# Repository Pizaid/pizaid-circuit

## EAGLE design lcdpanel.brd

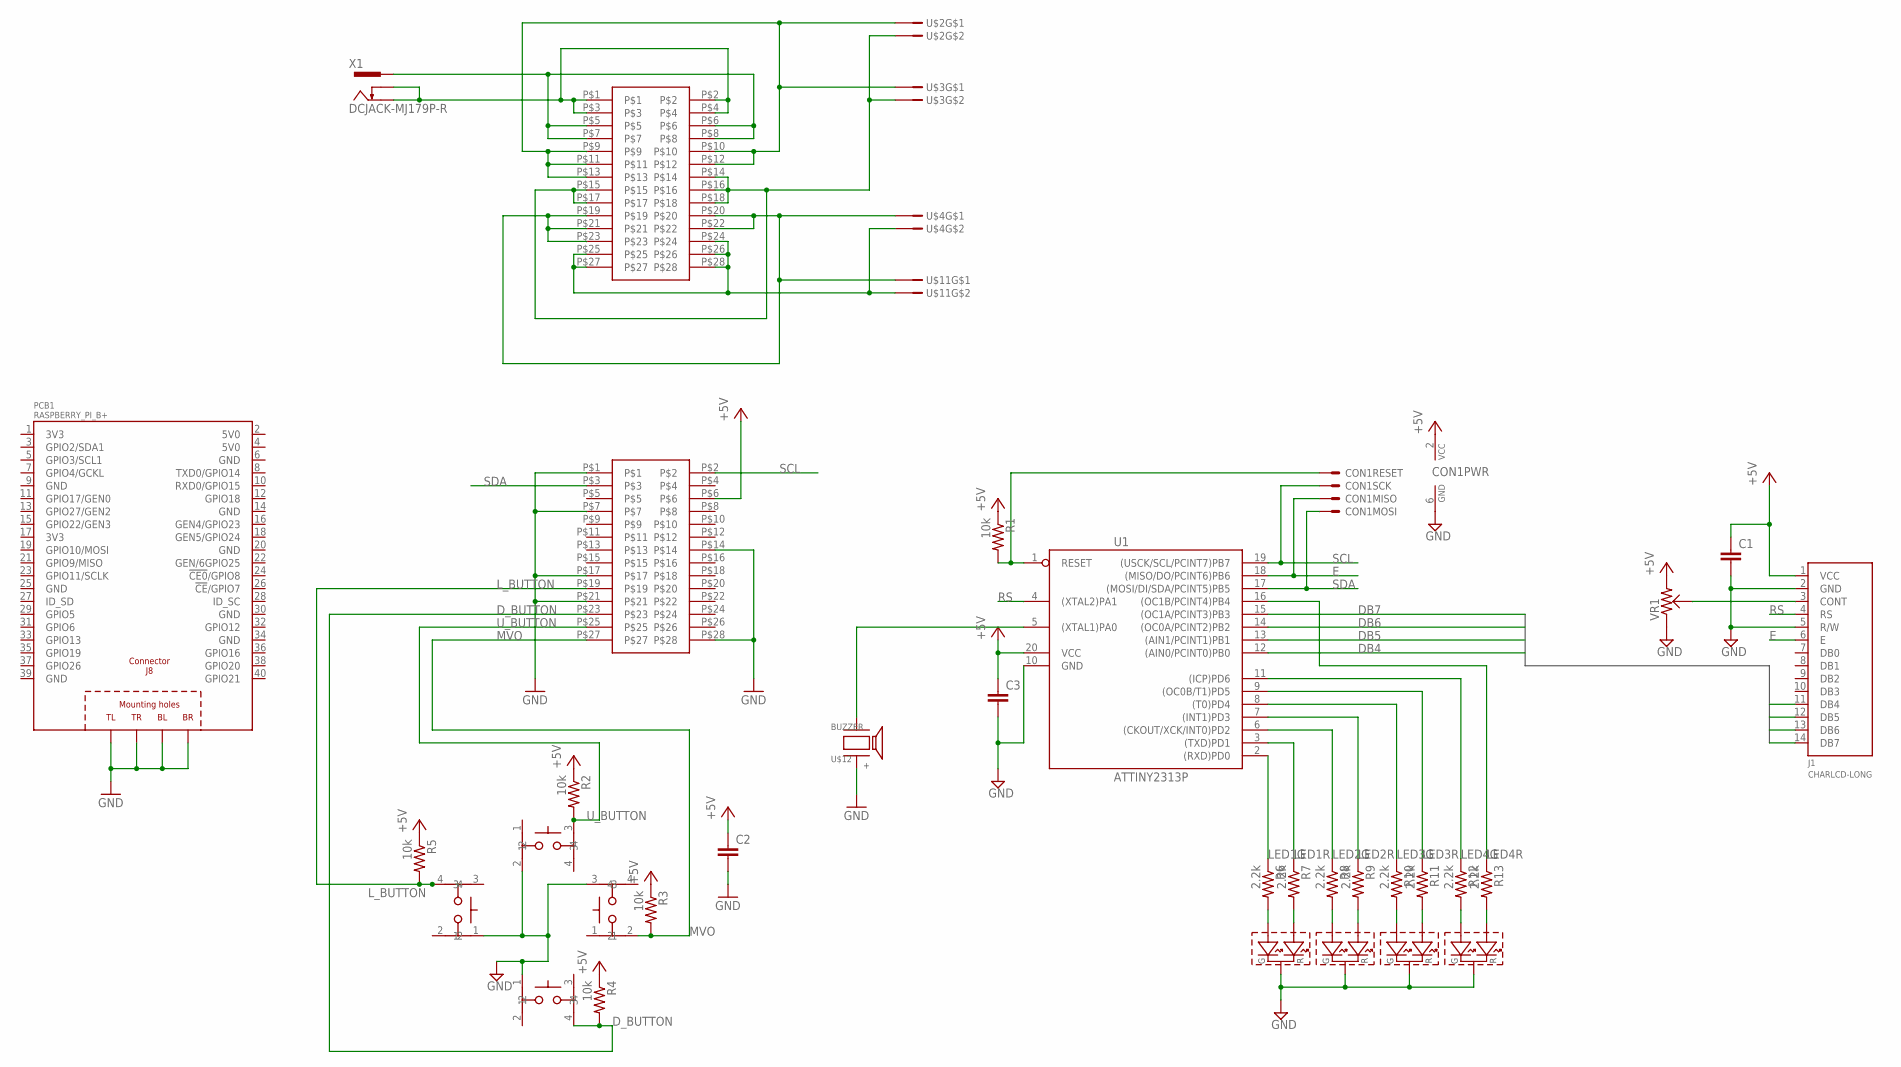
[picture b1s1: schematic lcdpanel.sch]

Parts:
C1, C2, C3: C-EUC0603; C0603
CON1: AVRISP-NEWSYMBOL-ML6; ML6
D1, D2, D3, D4: LED-RG-3MM; LED-2COL-3MM
J1: CHARLCD-LONG; CHARLCD-7X2-LONG
PCB1: RASPBERRY_PI_B+
R1, R2, R3, R4, R5: 10k; 1608
R6, R7, R8, R9, R10, R11, R12, R13: 2.2k; 1608
SW1, SW2, SW3, SW4: PUSHSW
U1: ATTINY2313P; DIL20
U$2, U$3, U$4, U$11: B2P-VH
U$12: BUZZER
U$13, U$14: CON_14X2
VR1: VR; VR-637A
X1: DCJACK-MJ179P-R; MJ-179P-R

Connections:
+5V: C1.1, C2.1, C3.1, CON1.2 (VCC), J1.1 (VCC), R1.1, R2.1, R3.1, R4.1, R5.1, U1.20 (VCC), U$13.P$6, VR1.2
DB4: J1.11 (DB4), U1.12 ((AIN0/PCINT0)PB0)
DB5: J1.12 (DB5), U1.13 ((AIN1/PCINT1)PB1)
DB6: J1.13 (DB6), U1.14 ((OC0A/PCINT2)PB2)
DB7: J1.14 (DB7), U1.15 ((OC1A/PCINT3)PB3)
D_BUTTON: R4.2, SW4.4, U$13.P$23
E: CON1.1 (S), J1.6 (E), U1.18 ((MISO/DO/PCINT6)PB6)
GND: C1.2, C2.2, C3.2, CON1.6 (GND), D1.K, D2.K, D3.K, D4.K, J1.2 (GND), J1.5 (R/W), PCB1.PE_BL (BL), PCB1.PE_BR (BR), PCB1.PE_TL (TL), PCB1.PE_TR (TR), SW1.2, SW2.1, SW3.3, SW4.1, U1.10 (GND), U$12.+, U$13.P$1, U$13.P$7, U$13.P$14, U$13.P$17, U$13.P$21, U$13.P$28, VR1.1
LED1G: R6.1, U1.2 ((RXD)PD0)
LED1R: R7.1, U1.3 ((TXD)PD1)
LED2G: R8.1, U1.6 ((CKOUT/XCK/INT0)PD2)
LED2R: R9.1, U1.7 ((INT1)PD3)
LED3G: R10.1, U1.8 ((T0)PD4)
LED3R: R11.1, U1.9 ((OC0B/T1)PD5)
LED4G: R12.1, U1.11 ((ICP)PD6)
LED4R: R13.1, U1.16 ((OC1B/PCINT4)PB4)
L_BUTTON: R5.2, SW2.4, U$13.P$19
MVO: R3.2, SW3.2, U$13.P$27
unnamed: CON1.5 (S), R1.2, U1.1 (RESET)
unnamed: U1.5 ((XTAL1)PA0), U$12.-
unnamed: J1.3 (CONT), VR1.BR
unnamed: D1.YG (G_A), R6.2
unnamed: D1.R (R_A), R7.2
unnamed: D2.YG (G_A), R8.2
unnamed: D3.YG (G_A), R10.2
unnamed: D3.R (R_A), R11.2
unnamed: D4.YG (G_A), R12.2
unnamed: D4.R (R_A), R13.2
unnamed: D2.R (R_A), R9.2
unnamed: U$14.P$5, U$14.P$6, U$14.P$7, U$14.P$8, X1.1
unnamed: U$2.P$1, U$3.P$1, U$14.P$9, U$14.P$10, U$14.P$11, U$14.P$12, U$14.P$13
unnamed: U$2.P$2, U$3.P$2, U$14.P$14, U$14.P$15, U$14.P$16, U$14.P$17, U$14.P$18
unnamed: U$4.P$2, U$11.P$2, U$14.P$24, U$14.P$25, U$14.P$26, U$14.P$27, U$14.P$28
unnamed: U$14.P$1, U$14.P$2, U$14.P$3, U$14.P$4, X1.2, X1.3
unnamed: U$4.P$1, U$11.P$1, U$14.P$19, U$14.P$20, U$14.P$21, U$14.P$22, U$14.P$23
RS: J1.4 (RS), U1.4 ((XTAL2)PA1)
SCL: CON1.3 (S), U1.19 ((USCK/SCL/PCINT7)PB7), U$13.P$2
SDA: CON1.4 (S), U1.17 ((MOSI/DI/SDA/PCINT5)PB5), U$13.P$3
U_BUTTON: R2.2, SW1.3, U$13.P$25

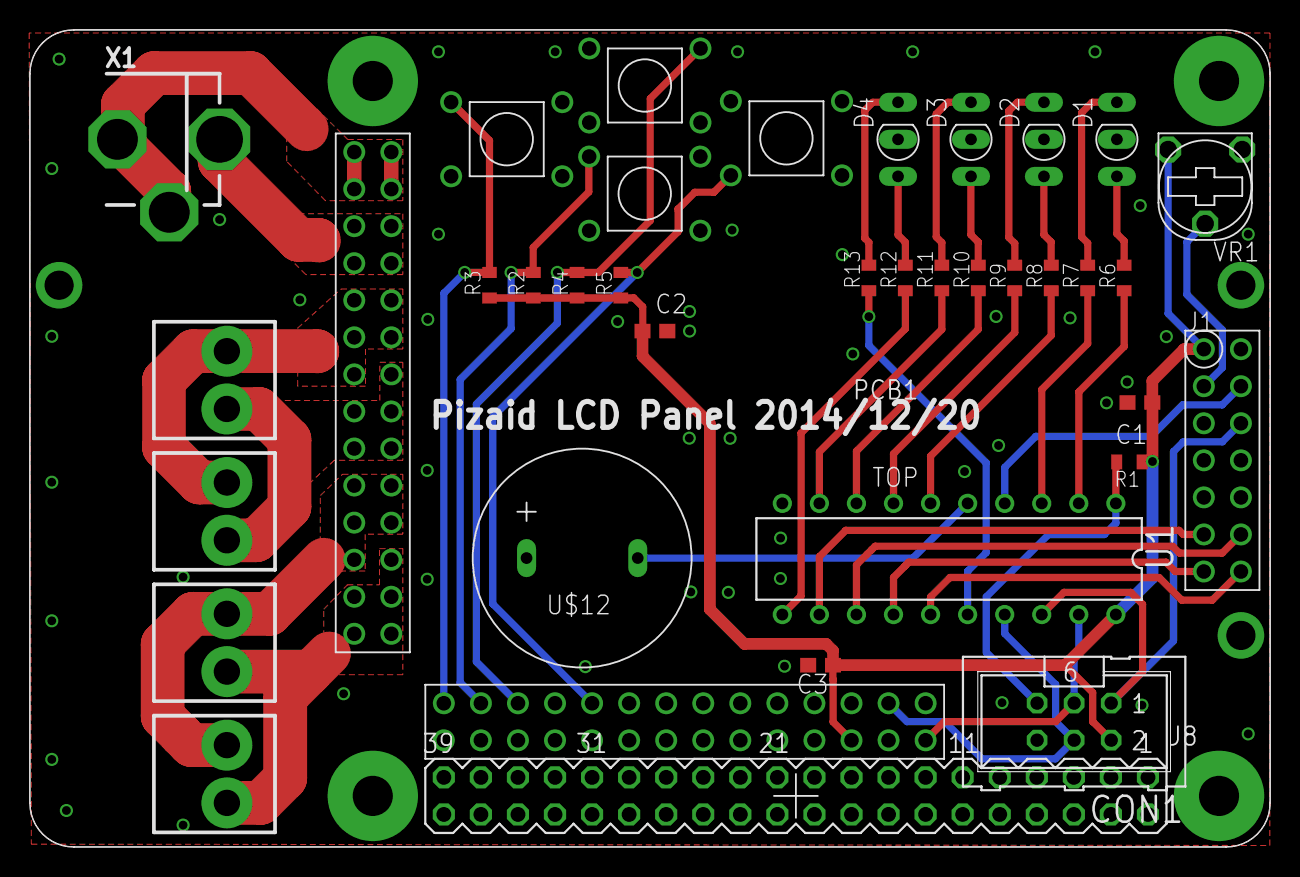
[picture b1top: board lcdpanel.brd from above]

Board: 2 copper layers, 85.0 x 56.0 mm, 37 parts (0 on the bottom side), 39 nets.

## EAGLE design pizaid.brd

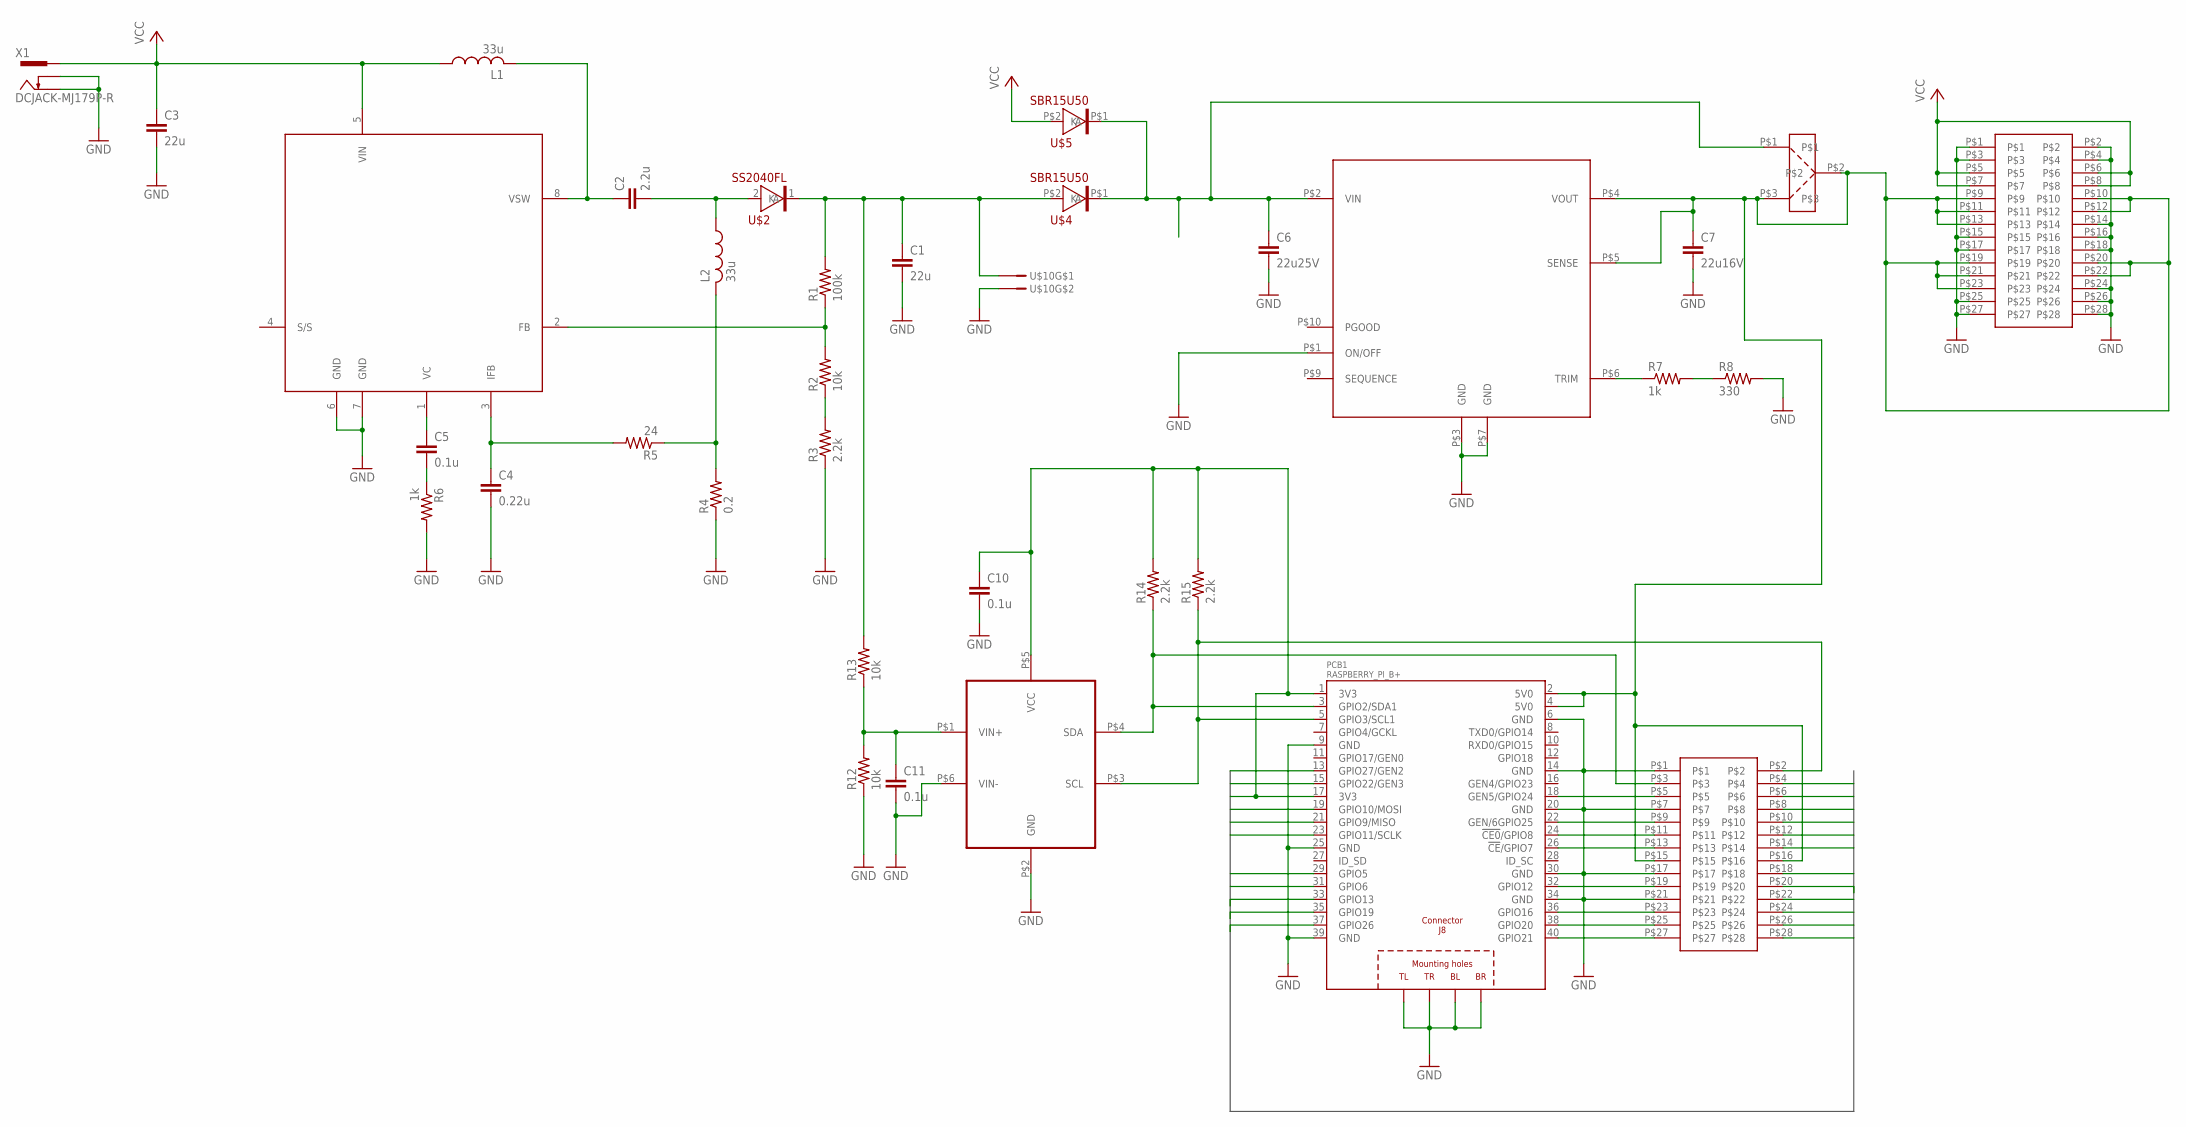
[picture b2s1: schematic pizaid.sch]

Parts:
C1, C3: 22u; C3225
C2: 2.2u; C3216
C4: 0.22u; C0603
C5, C10, C11: 0.1u; C0603
C6: 22u25V; C3225
C7: 22u16V; C3225
L1, L2: 33u; L5650M
PCB1: RASPBERRY_PI_B+
R1: 100k; R0603
R2, R12, R13: 10k; R0603
R3, R14, R15: 2.2k; R0603
R4: 0.2; 0207/15
R5: 24; R0603
R6, R7: 1k; R0603
R8: 330; R0603
U$1: LT1512CS8; SOP8
U$2: SS2040FL; SOD-123FL
U$3, U$8: CON_14X2
U$4, U$5: SBR15U50; POWERDI5
U$6: OKL-T/6
U$9: MCP3425; SOT-23-6
U$10: B2P-VH
U$11: SELECT_PAD
X1: DCJACK-MJ179P-R; MJ-179P-R

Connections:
5V0@2: C7.1, PCB1.2 (5V0), PCB1.4 (5V0), U$3.P$9, U$3.P$10, U$3.P$11, U$3.P$12, U$3.P$13, U$3.P$19, U$3.P$20, U$3.P$21, U$3.P$22, U$3.P$23, U$6.P$4 (VOUT), U$6.P$5 (SENSE), U$8.P$15, U$8.P$16, U$11.P$2, U$11.P$3
B1: PCB1.15 (GPIO22/GEN3), U$8.P$4
B2: C10.1, PCB1.1 (3V3), PCB1.17 (3V3), R14.2, R15.2, U$8.P$6, U$9.P$5 (VCC)
B3: PCB1.19 (GPIO10/MOSI), U$8.P$8
B4: PCB1.21 (GPIO9/MISO), U$8.P$10
B5: PCB1.23 (GPIO11/SCLK), U$8.P$12
B6: U$8.P$14
B8: PCB1.29 (GPIO5), U$8.P$18
B9: PCB1.31 (GPIO6), U$8.P$20
B10: PCB1.33 (GPIO13), U$8.P$22
B11: PCB1.35 (GPIO19), U$8.P$24
B12: PCB1.37 (GPIO26), U$8.P$26
B13: U$8.P$28
B$1: PCB1.13 (GPIO27/GEN2)
GIRD: C6.1, U$4.P$1 (K), U$5.P$1 (K), U$6.P$2 (VIN), U$11.P$1
GND: C1.2, C3.2, C4.2, C6.2, C7.2, C10.2, C11.2, PCB1.6 (GND), PCB1.9 (GND), PCB1.14 (GND), PCB1.20 (GND), PCB1.25 (GND), PCB1.30 (GND), PCB1.34 (GND), PCB1.39 (GND), PCB1.PE_BL (BL), PCB1.PE_BR (BR), PCB1.PE_TL (TL), PCB1.PE_TR (TR), R3.1, R4.1, R6.2, R8.2, R12.1, U$1.6 (GND), U$1.7 (GND), U$3.P$1, U$3.P$2, U$3.P$3, U$3.P$4, U$3.P$14, U$3.P$15, U$3.P$16, U$3.P$17, U$3.P$18, U$3.P$24, U$3.P$25, U$3.P$26, U$3.P$27, U$3.P$28, U$6.P$1 (ON/OFF), U$6.P$3 (GND), U$6.P$7 (GND), U$8.P$1, U$8.P$7, U$8.P$17, U$8.P$21, U$9.P$2 (GND), U$9.P$6 (VIN-), U$10.P$2, X1.2, X1.3
unnamed: R2.1, R3.2
unnamed: C2.1, L1.2, U$1.8 (VSW)
unnamed: C1.1, R1.2, R13.2, U$2.1 (K), U$4.P$2 (A), U$10.P$1
unnamed: L2.2, R4.2, R5.1
unnamed: C4.1, R5.2, U$1.3 (IFB)
unnamed: C5.1, U$1.1 (VC)
unnamed: C5.2, R6.1
unnamed: PCB1.40 (GPIO21), U$8.P$27
unnamed: R1.1, R2.2, U$1.2 (FB)
unnamed: C2.2, L2.1, U$2.2 (A)
unnamed: PCB1.38 (GPIO20), U$8.P$25
unnamed: PCB1.5 (GPIO3/SCL1), R15.1, U$8.P$2, U$9.P$3 (SCL)
unnamed: R7.1, U$6.P$6 (TRIM)
unnamed: R7.2, R8.1
unnamed: C11.1, R12.2, R13.1, U$9.P$1 (VIN+)
unnamed: PCB1.3 (GPIO2/SDA1), R14.1, U$8.P$3, U$9.P$4 (SDA)
unnamed: PCB1.36 (GPIO16), U$8.P$23
unnamed: PCB1.32 (GPIO12), U$8.P$19
unnamed: PCB1.26 (!CE!/GPIO7), U$8.P$13
unnamed: PCB1.24 (!CE0!/GPIO8), U$8.P$11
unnamed: PCB1.22 (GEN/6GPIO25), U$8.P$9
unnamed: PCB1.18 (GEN5/GPIO24), U$8.P$5
VCC: C3.1, L1.1, U$1.5 (VIN), U$3.P$5, U$3.P$6, U$3.P$7, U$3.P$8, U$5.P$2 (A), X1.1

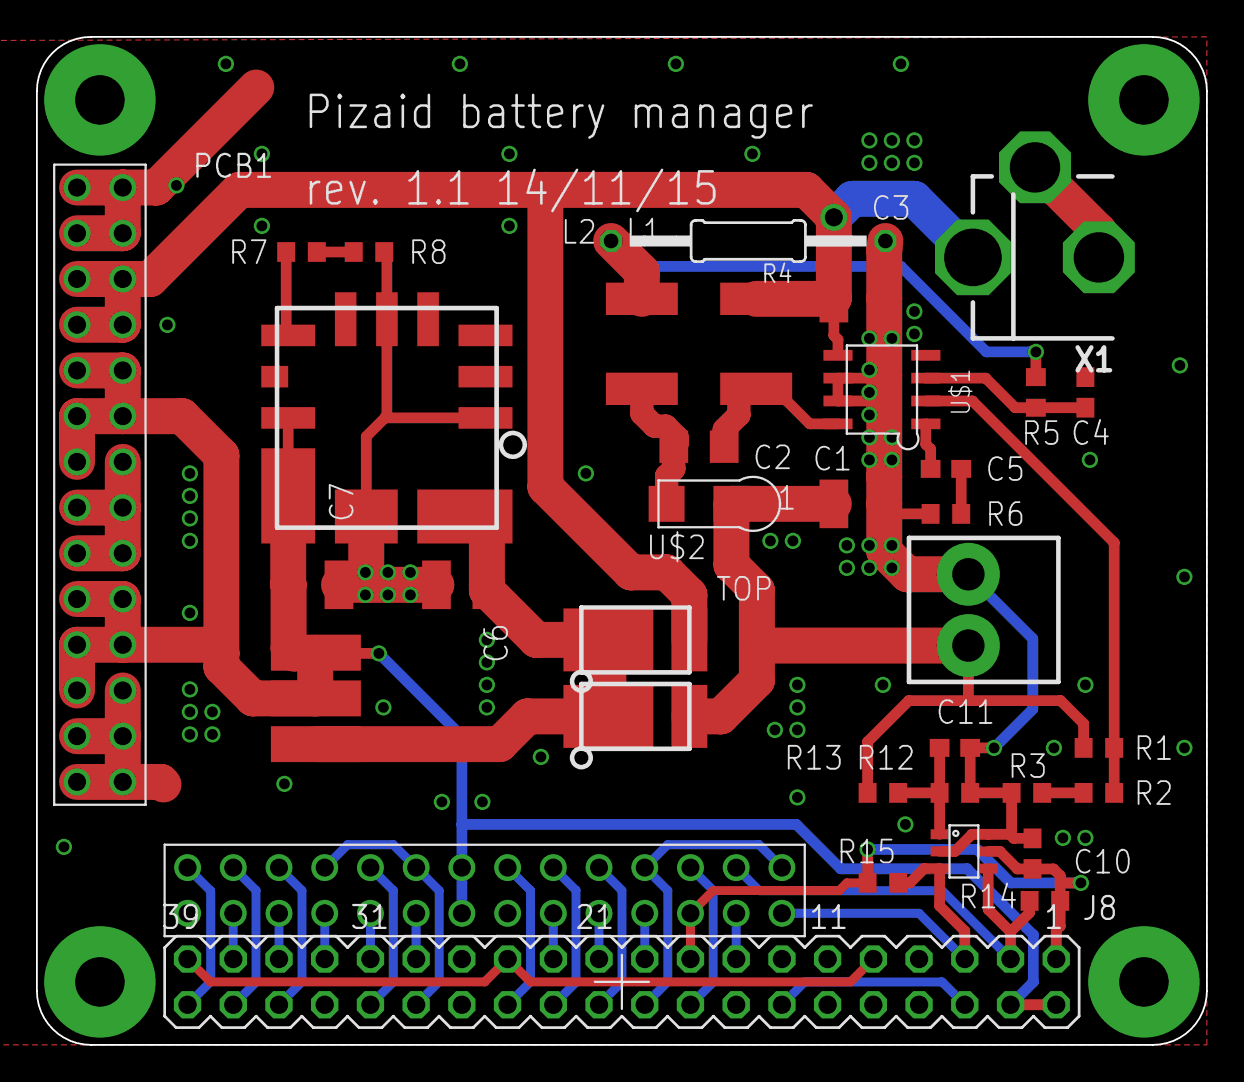
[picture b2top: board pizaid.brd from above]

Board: 4 copper layers, 65.0 x 56.0 mm, 35 parts (0 on the bottom side), 36 nets.

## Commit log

2014-08-02 supported Raspberry Pi model B+
2014-08-02 cleaned backup files
2014-08-09 added gerber and con-jst.lbr
2014-08-09 added part info
2014-08-09 Add LCD
2014-08-09 changed dcjack
2014-08-09 modified to two-layer pcb and generated gerber for fusion
2014-08-09 cleaned board
2014-08-09 ぐらんどきれいにした
2014-08-09 がーばーあっぷでーと
2014-08-09 modified board outline
2014-08-10 Add 3mm 2colors LED
2014-08-10 corrected a small mistake
2014-08-10 Add LCD Panel
2014-08-10 modified board for stacking (ontheway)
2014-08-10 added top board (ontheway)
2014-08-15 continuing placement.....................
2014-09-01 airwireが表示されないくてよくわかんない
2014-09-01 draw stackable lcdpanel, not yet completed
2014-09-14 updated second layer
2014-10-01 completed rev1
2014-10-01 added gerber
2014-11-15 fixed reversed connector on lcdpanel
2014-11-15 modified battery board to output 12V
2014-12-06 add default output jumper to 5V
2014-12-20 add AVR and bug fix
